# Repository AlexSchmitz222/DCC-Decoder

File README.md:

# DCC-Decoder
DIY DCC Decoder with 16 Outputs for Use with MARDEC or ARSIGDEC Software by ArCoMoRa (https://www.arcomora.com/)

License Model: CC BY-NC-ND (https://creativecommons.org/licenses/by-nc-nd/4.0/legalcode / https://creativecommons.org/licenses/by-nc-nd/4.0/) 

Made by AlexSchmitz222 & JayReturns

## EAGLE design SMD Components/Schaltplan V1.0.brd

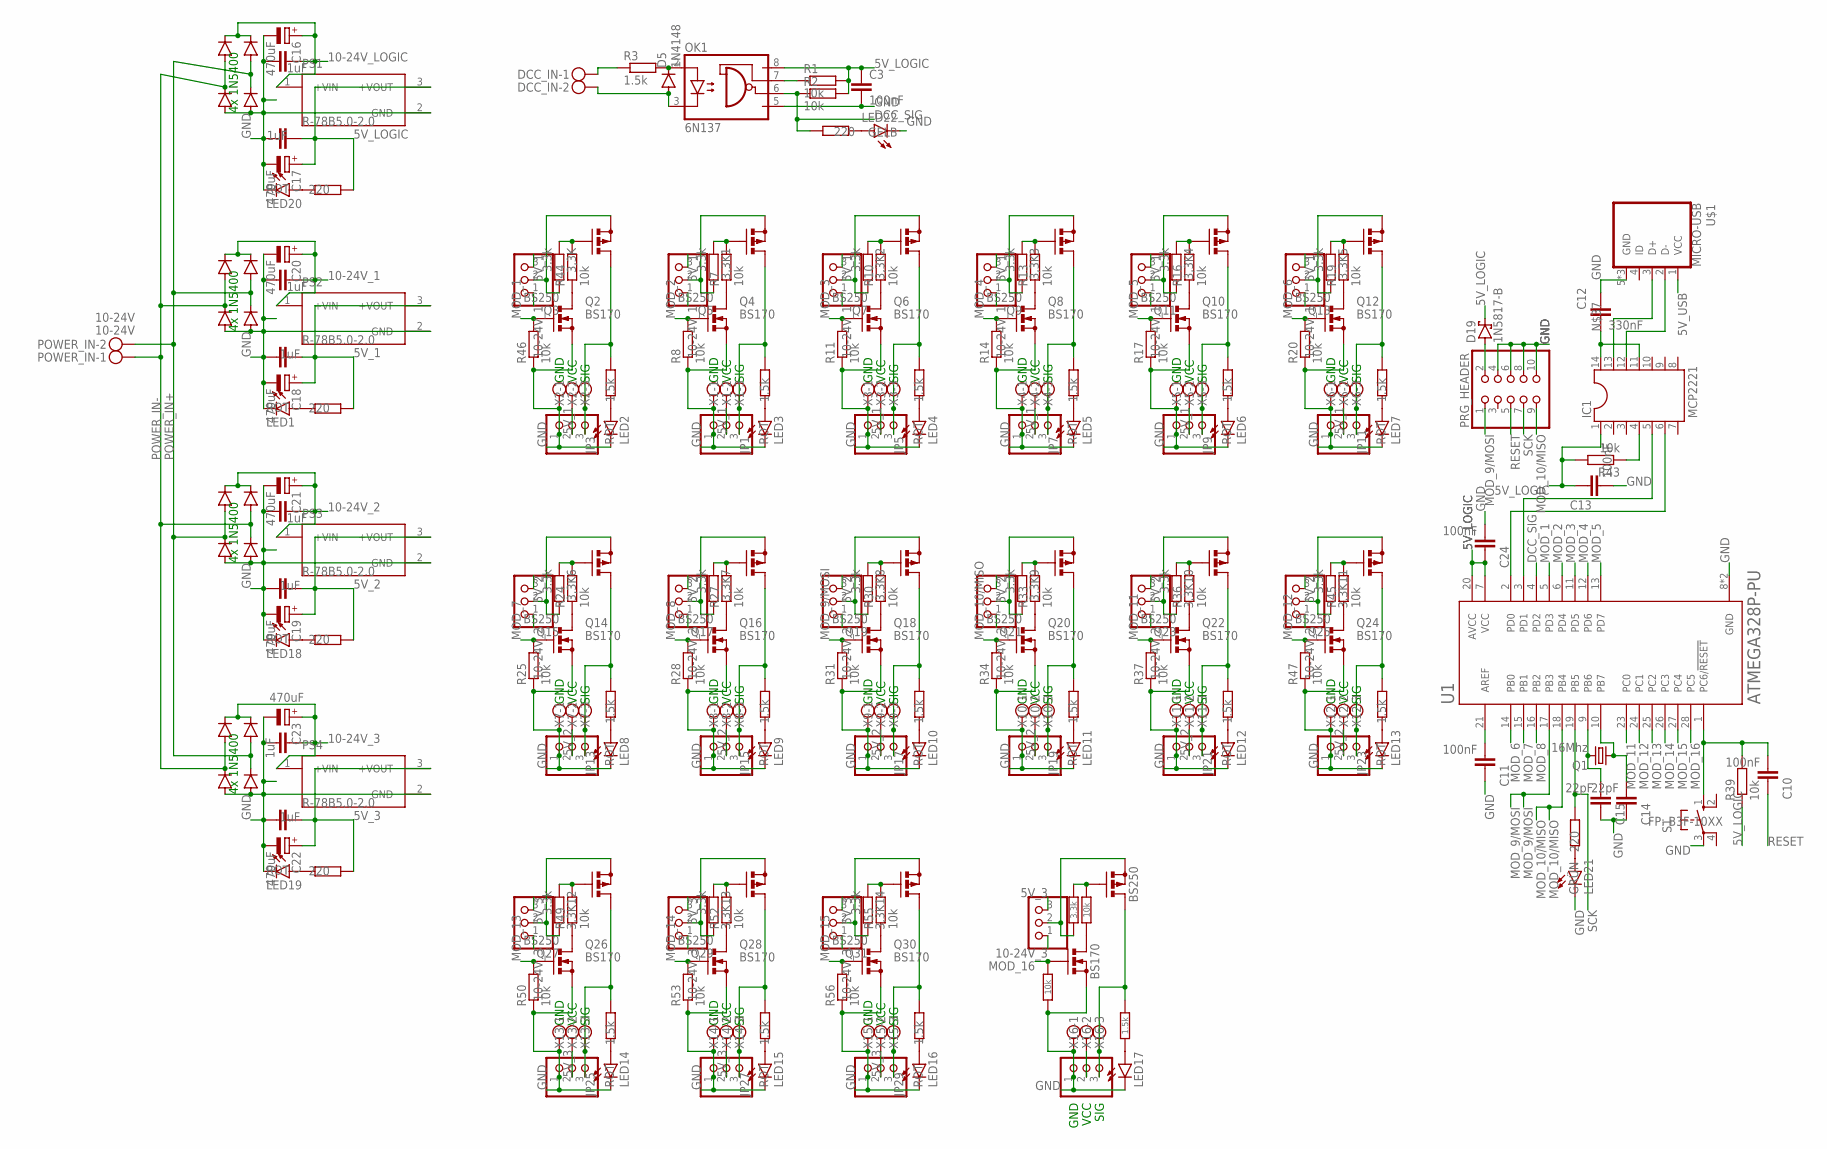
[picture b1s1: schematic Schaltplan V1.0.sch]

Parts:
3,3K, 3,3K1, 3,3K2, 3,3K3, 3,3K4, 3,3K5, 3,3K6, 3,3K7, 3,3K8, 3,3K9, 3,3K10, 3,3K11, 3,3K12, 3,3K13, 3,3K14, 3,3K15: 3.3k; 0207/7
C1, C2, C4, C5, C6, C7, C8, C9: 1uF; C050-025X075
C3, C10, C11, C13, C24: 100nF; C025-025X050
C12: 330nF; C025-025X050
C14, C15: 22pF; C025-030X050
C16, C17, C18, C19, C20, C21, C22, C23: 470uF; E5-10,5
D1, D2, D3, D4, D6, D7, D8, D9, D10, D11, D12, D13, D14, D15, D16, D17: 1N5400; DO201-15
D5: 1N4148; DO35-7
D19: 1N5817-B; DO41-7.6
DCC_IN: MKDSN1,5/2-5,08
IC1: MCP2221; DIL14
JP1, JP2, JP3, JP4, JP5, JP6, JP7, JP8, JP9, JP10, JP11, JP12, JP13, JP14, JP15, JP16, JP17, JP18, JP19, JP20, JP21, JP22, JP23, JP24, JP25, JP26, JP27, JP28, JP29, JP30, JP31, JP32: PINHD-1X3; 1X03
LED1, LED2, LED3, LED4, LED5, LED6, LED7, LED8, LED9, LED10, LED11, LED12, LED13, LED14, LED15, LED16, LED17, LED18, LED19, LED20: ROT; LED3MM
LED21: GRÜN; LED3MM
LED22: GELB; LED3MM
OK1: 6N137; DIL08
POWER_IN: 10-24V; MKDSN1,5/2-5,08
PRG_HEADER: PINHD-2X5; 2X05
PS1, PS2, PS3, PS4: R-78B5.0-2.0; CONV_R-78B5.0-2.0
Q1: 16Mhz; HC49U-V
Q2, Q4, Q6, Q8, Q10, Q12, Q14, Q16, Q18, Q20, Q22, Q24, Q26, Q28, Q30, Q32: BS170; SOT54E
Q3, Q5, Q7, Q9, Q11, Q13, Q15, Q17, Q19, Q21, Q23, Q25, Q27, Q29, Q31, Q33: BS250; SOT54E
R1, R2, R7, R8, R10, R11, R13, R14, R16, R17, R19, R20, R24, R25, R27, R28, R30, R31, R33, R34, R36, R37, R39, R43, R44, R45, R46, R47, R49, R50, R52, R53, R55, R56, R58, R59: 10k; 0207/7
R3, R5, R6, R9, R12, R15, R18, R23, R26, R29, R32, R35, R38, R48, R51, R54, R57: 1.5k; 0207/7
R4, R21, R22, R40, R41, R42: 220; 0207/7
S1: FP: B3F-10XX; B3F-10XX
U1: ATMEGA328P-PU; DIP794W46P254L2967H457Q28B
U$1: MICRO-USB
X1, X2, X3, X4, X5, X6, X7, X8, X9, X10, X11, X12, X13, X14, X15, X16: MKDSN1,5/3-5,08

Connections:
5V_1: C1.2, C18.+, JP1.2, JP2.3, JP3.2, JP4.3, JP5.2, JP6.3, JP7.2, JP8.3, JP9.2, JP10.3, JP11.2, JP12.3, PS2.3 (+VOUT), R4.2, X1.2, X2.2, X3.2, X4.2, X5.2, X6.2
5V_2: C4.2, C19.+, JP13.2, JP14.3, JP15.2, JP16.3, JP17.2, JP18.3, JP19.2, JP20.3, JP21.2, JP22.3, JP23.2, JP24.3, PS3.3 (+VOUT), R21.2, X7.2, X8.2, X9.2, X10.2, X11.2, X12.2
5V_3: C6.2, C22.+, JP25.2, JP26.3, JP27.2, JP28.3, JP29.2, JP30.3, JP31.2, JP32.3, PS4.3 (+VOUT), R22.2, X13.2, X14.2, X15.2, X16.2
5V_LOGIC: C3.1, C8.2, C13.1, C17.+, C24.1, D19.C, IC1.1, OK1.8 (VCC), PS1.3 (+VOUT), R1.2, R2.2, R39.1, R40.2, R43.2, U1.7 (VCC), U1.20 (AVCC)
5V_USB: U$1.1 (VCC)
10-24V_1: C2.2, C20.+, D1.C, D3.C, JP2.1, JP4.1, JP6.1, JP8.1, JP10.1, JP12.1, PS2.1 (+VIN)
10-24V_2: C5.2, C21.+, D6.C, D8.C, JP14.1, JP16.1, JP18.1, JP20.1, JP22.1, JP24.1, PS3.1 (+VIN)
10-24V_3: C7.2, C23.+, D10.C, D12.C, JP26.1, JP28.1, JP30.1, JP32.1, PS4.1 (+VIN)
10-24V_LOGIC: C9.2, C16.+, D14.C, D16.C, PS1.1 (+VIN)
AREF: C11.2, U1.21 (AREF)
DCC_SIG: OK1.6 (VO), R2.1, R42.2, U1.4 (PD2)
GND: C1.1, C2.1, C3.2, C4.1, C5.1, C6.1, C7.1, C8.1, C9.1, C11.1, C12.1, C13.2, C14.1, C15.1, C16.-, C17.-, C18.-, C19.-, C20.-, C21.-, C22.-, C23.-, C24.2, D2.A, D4.A, D7.A, D9.A, D11.A, D13.A, D15.A, D17.A, JP1.1, JP3.1, JP5.1, JP7.1, JP9.1, JP11.1, JP13.1, JP15.1, JP17.1, JP19.1, JP21.1, JP23.1, JP25.1, JP27.1, JP29.1, JP31.1, LED1.K (C), LED2.K (C), LED3.K (C), LED4.K (C), LED5.K (C), LED6.K (C), LED7.K (C), LED8.K (C), LED9.K (C), LED10.K (C), LED11.K (C), LED12.K (C), LED13.K (C), LED14.K (C), LED15.K (C), LED16.K (C), LED17.K (C), LED18.K (C), LED19.K (C), LED20.K (C), LED21.K (C), LED22.K (C), OK1.5 (GND), PRG_HEADER.4, PRG_HEADER.6, PRG_HEADER.8, PRG_HEADER.10, PS1.2 (GND), PS2.2 (GND), PS3.2 (GND), PS4.2 (GND), Q2.S, Q4.S, Q6.S, Q8.S, Q10.S, Q12.S, Q14.S, Q16.S, Q18.S, Q20.S, Q22.S, Q24.S, Q26.S, Q28.S, Q30.S, Q32.S, R8.1, R11.1, R14.1, R17.1, R20.1, R25.1, R28.1, R31.1, R34.1, R37.1, R46.1, R47.1, R50.1, R53.1, R56.1, R59.1, S1.3, U1.8 (GND), U1.22 (GND), U$1.5 (GND), U$1.GND1 (GND), U$1.GND2 (GND), X1.1, X2.1, X3.1, X4.1, X5.1, X6.1, X7.1, X8.1, X9.1, X10.1, X11.1, X12.1, X13.1, X14.1, X15.1, X16.1
MOD_1: Q2.G, R46.2, U1.5 (PD3)
MOD_2: Q4.G, R8.2, U1.6 (PD4)
MOD_3: Q6.G, R11.2, U1.11 (PD5)
MOD_4: Q8.G, R14.2, U1.12 (PD6)
MOD_5: Q10.G, R17.2, U1.13 (PD7)
MOD_6: Q12.G, R20.2, U1.14 (PB0)
MOD_7: Q14.G, R25.2, U1.15 (PB1)
MOD_8: Q16.G, R28.2, U1.16 (PB2)
MOD_9/MOSI: PRG_HEADER.1, Q18.G, R31.2, U1.17 (PB3)
MOD_10/MISO: PRG_HEADER.9, Q20.G, R34.2, U1.18 (PB4)
MOD_11: Q22.G, R37.2, U1.23 (PC0)
MOD_12: Q24.G, R47.2, U1.24 (PC1)
MOD_13: Q26.G, R50.2, U1.25 (PC2)
MOD_14: Q28.G, R53.2, U1.26 (PC3)
MOD_15: Q30.G, R56.2, U1.27 (PC4)
MOD_16: Q32.G, R59.2, U1.28 (PC5)
unnamed: DCC_IN.1, R3.1
unnamed: LED1.A, R4.1
unnamed: LED18.A, R21.1
unnamed: D5.C, OK1.2 (A), R3.2
unnamed: JP3.3, Q3.D, R5.2, X2.3
unnamed: JP1.3, Q5.D, R6.2, X1.3
unnamed: LED19.A, R22.1
unnamed: OK1.7 (VE), R1.1
unnamed: 3,3K13.1, Q29.G, R52.2
unnamed: LED20.A, R40.1
unnamed: LED3.A, R6.1
unnamed: 3,3K.2, JP4.2, Q3.S
unnamed: LED2.A, R5.1
unnamed: LED21.A, R41.1
unnamed: 3,3K12.1, Q27.G, R49.2
unnamed: Q4.D, R7.1
unnamed: LED22.A, R42.1
unnamed: 3,3K1.2, JP2.2, Q5.S
unnamed: JP5.3, Q7.D, R9.2, X3.3
unnamed: LED4.A, R9.1
unnamed: IC1.5, U1.3 (PD1)
unnamed: Q2.D, R44.1
unnamed: IC1.4, R43.1
unnamed: IC1.13, U$1.3 (D+)
unnamed: 3,3K14.1, Q31.G, R55.2
unnamed: Q6.D, R10.1
unnamed: 3,3K2.2, JP6.2, Q7.S
unnamed: JP7.3, Q9.D, R12.2, X4.3
unnamed: IC1.6, U1.2 (PD0)
unnamed: IC1.12, U$1.2 (D-)
unnamed: LED5.A, R12.1
unnamed: 3,3K15.1, Q33.G, R58.2
unnamed: Q8.D, R13.1
unnamed: C12.2, IC1.11, IC1.14
unnamed: D19.A, PRG_HEADER.2
unnamed: 3,3K3.2, JP8.2, Q9.S
unnamed: JP9.3, Q11.D, R15.2, X5.3
unnamed: LED6.A, R15.1
unnamed: Q10.D, R16.1
unnamed: 3,3K4.2, JP10.2, Q11.S
unnamed: JP11.3, Q13.D, R18.2, X6.3
unnamed: LED7.A, R18.1
unnamed: Q12.D, R19.1
unnamed: D5.A, DCC_IN.2, OK1.3 (C)
unnamed: 3,3K5.2, JP12.2, Q13.S
unnamed: JP13.3, Q15.D, R23.2, X7.3
unnamed: LED8.A, R23.1
unnamed: 3,3K5.1, Q13.G, R19.2
unnamed: Q14.D, R24.1
unnamed: 3,3K6.2, JP14.2, Q15.S
unnamed: JP15.3, Q17.D, R26.2, X8.3
unnamed: LED9.A, R26.1
unnamed: 3,3K4.1, Q11.G, R16.2
unnamed: Q16.D, R27.1
unnamed: 3,3K7.2, JP16.2, Q17.S
unnamed: JP17.3, Q19.D, R29.2, X9.3
unnamed: LED10.A, R29.1
unnamed: 3,3K3.1, Q9.G, R13.2
unnamed: Q18.D, R30.1
unnamed: 3,3K8.2, JP18.2, Q19.S
unnamed: JP19.3, Q21.D, R32.2, X10.3
unnamed: LED11.A, R32.1
unnamed: 3,3K10.1, Q23.G, R36.2
unnamed: Q20.D, R33.1
unnamed: 3,3K9.2, JP20.2, Q21.S
unnamed: JP21.3, Q23.D, R35.2, X11.3
unnamed: LED12.A, R35.1
unnamed: 3,3K2.1, Q7.G, R10.2
unnamed: Q22.D, R36.1
unnamed: 3,3K10.2, JP22.2, Q23.S
unnamed: JP23.3, Q25.D, R38.2, X12.3
unnamed: LED13.A, R38.1
unnamed: 3,3K1.1, Q5.G, R7.2
unnamed: Q24.D, R45.1
unnamed: 3,3K11.2, JP24.2, Q25.S
unnamed: JP25.3, Q27.D, R48.2, X13.3
unnamed: LED14.A, R48.1
unnamed: Q26.D, R49.1
unnamed: 3,3K12.2, JP26.2, Q27.S
unnamed: JP27.3, Q29.D, R51.2, X14.3
unnamed: LED15.A, R51.1
unnamed: Q28.D, R52.1
unnamed: 3,3K13.2, JP28.2, Q29.S
unnamed: JP29.3, Q31.D, R54.2, X15.3
unnamed: LED16.A, R54.1
unnamed: Q30.D, R55.1
unnamed: 3,3K14.2, JP30.2, Q31.S
unnamed: JP31.3, Q33.D, R57.2, X16.3
unnamed: LED17.A, R57.1
unnamed: Q32.D, R58.1
unnamed: 3,3K15.2, JP32.2, Q33.S
unnamed: 3,3K9.1, Q21.G, R33.2
unnamed: 3,3K11.1, Q25.G, R45.2
unnamed: 3,3K8.1, Q19.G, R30.2
unnamed: 3,3K7.1, Q17.G, R27.2
unnamed: 3,3K6.1, Q15.G, R24.2
unnamed: 3,3K.1, Q3.G, R44.2
POWER_IN+: D3.A, D4.C, D6.A, D7.C, D12.A, D13.C, D16.A, D17.C, POWER_IN.2
POWER_IN-: D1.A, D2.C, D8.A, D9.C, D10.A, D11.C, D14.A, D15.C, POWER_IN.1
QUARTZ_1: C15.2, Q1.2, U1.9 (PB6)
QUARTZ_2: C14.2, Q1.1, U1.10 (PB7)
RESET: C10.1, PRG_HEADER.5
RESET_MC: C10.2, R39.2, S1.1 (S), U1.1 (PC6/!RESET)
SCK: PRG_HEADER.7, R41.2, U1.19 (PB5)

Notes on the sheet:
4x 1N5400
SIG
VCC
GND

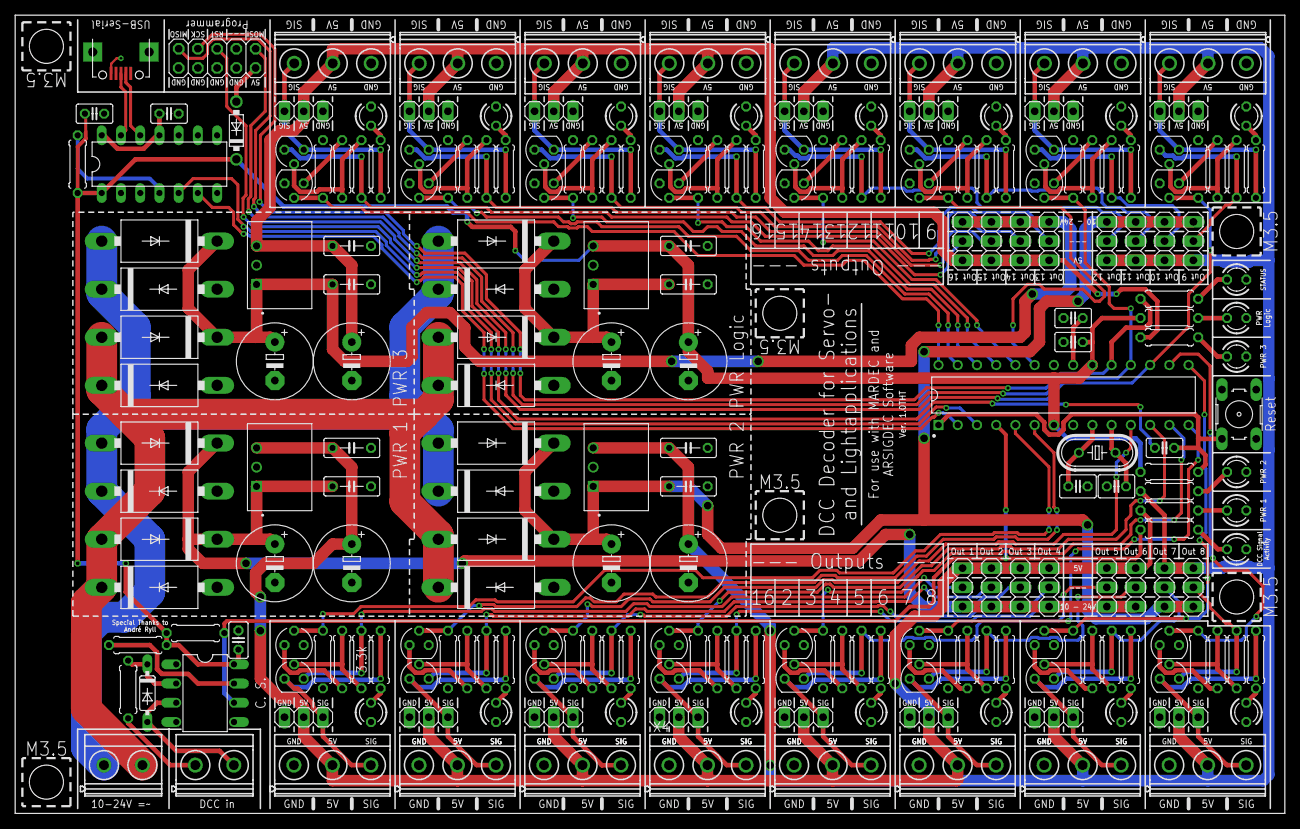
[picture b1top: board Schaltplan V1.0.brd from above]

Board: 2 copper layers, 167.7 x 105.4 mm, 232 parts (0 on the bottom side), 131 nets.

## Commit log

2022-02-04 Initial Push of Schematic and Layout (only THT Components)
2022-02-04 Update README.md
    Added License Model
2022-02-05 Improved project structure
2022-02-05 added SMD Variant
2022-02-06 added SMD Parts
2022-02-06 fixed Parts List
